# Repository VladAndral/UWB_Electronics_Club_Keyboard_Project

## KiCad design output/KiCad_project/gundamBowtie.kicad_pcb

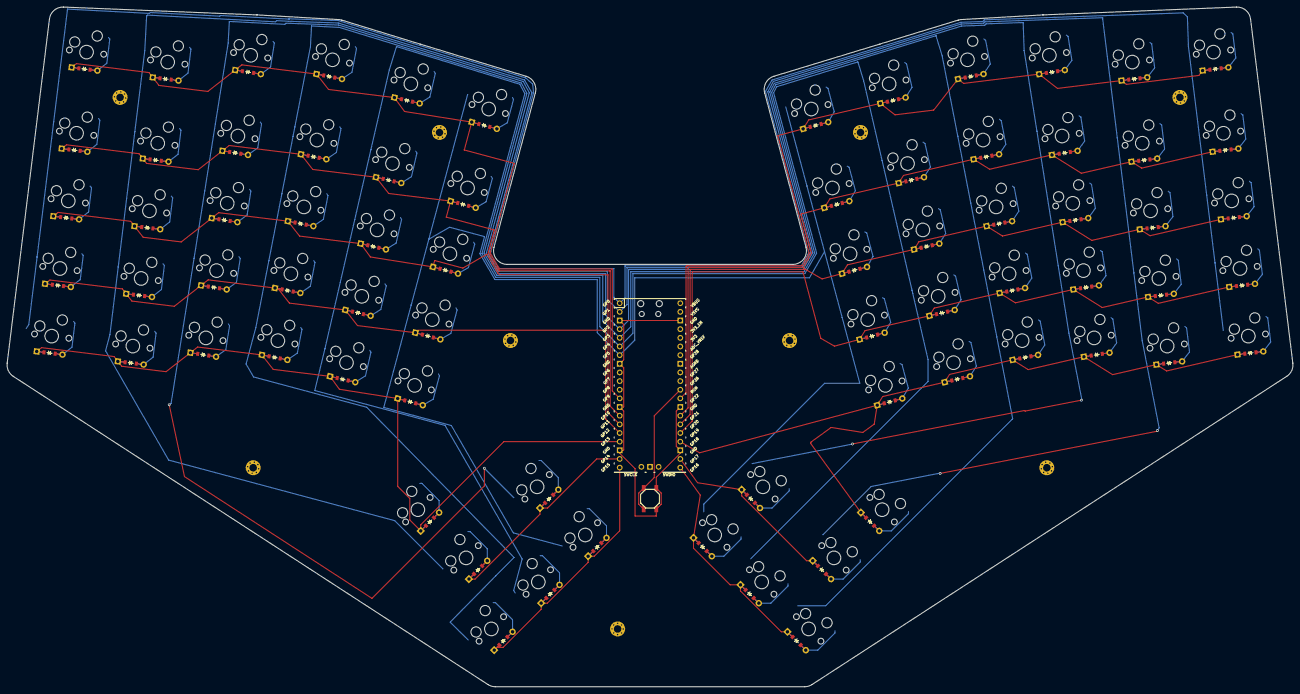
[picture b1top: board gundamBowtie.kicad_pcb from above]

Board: 2 copper layers, 377.5 x 199.5 mm, 155 parts (0 on the bottom side), 94 nets.

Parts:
B1: SW_TACT_ALPS_SKQGABE010
D1, D2, D3, D4, D5, D6, D7, D8, D9, D10, D11, D12, D13, D14, D15, D16, D17, D18, D19, D20, D21, D22, D23, D24, D25, D26, D27, D28, D29, D30, D31, D32, D33, D34, D35, D36, D37, D38, D39, D40, D41, D42, D43, D44, D45, D46, D47, D48, D49, D50, D51, D52, D53, D54, D55, D56, D57, D58, D59, D60, D61, D62, D63, D64, D65, D66, D67, D68, D69, D70, D71, D72: ComboDiode
S1, S2, S3, S4, S5, S6, S7, S8, S9, S10, S11, S12, S13, S14, S15, S16, S17, S18, S19, S20, S21, S22, S23, S24, S25, S26, S27, S28, S29, S30, S31, S32, S33, S34, S35, S36, S37, S38, S39, S40, S41, S42, S43, S44, S45, S46, S47, S48, S49, S50, S51, S52, S53, S54, S55, S56, S57, S58, S59, S60, S61, S62, S63, S64, S65, S66, S67, S68, S69, S70, S71, S72: MX
_1: RPi_Pico_SMD_TH
_2, _3, _4, _5, _6, _7, _8, _9, _10: MountingHole_2.2mm_M2_Pad_Via

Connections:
GND: B1.1, _1.3, _1.8, _1.13, _1.18, _1.23, _1.28, _1.38
GP0: S1.1, S2.1, S3.1, S4.1, S5.1, S37.1, S38.1, S39.1, S40.1, S41.1, _1.1
GP1: S6.1, S7.1, S8.1, S9.1, S10.1, S31.1, S32.1, S42.1, S43.1, S44.1, S45.1, S46.1, S67.1, S68.1, _1.2
GP2: S11.1, S12.1, S13.1, S14.1, S15.1, S33.1, S47.1, S48.1, S49.1, S50.1, S51.1, S69.1, _1.4
GP3: S16.1, S17.1, S18.1, S19.1, S20.1, S34.1, S52.1, S53.1, S54.1, S55.1, S56.1, S70.1, _1.5
GP4: S21.1, S22.1, S23.1, S24.1, S25.1, S35.1, S57.1, S58.1, S59.1, S60.1, S61.1, S71.1, _1.6
GP5: S26.1, S27.1, S28.1, S29.1, S30.1, S36.1, S62.1, S63.1, S64.1, S65.1, S66.1, S72.1, _1.7
GP9: D5.1, D10.1, D15.1, D20.1, D25.1, D30.1, _1.12
GP10: D4.1, D9.1, D14.1, D19.1, D24.1, D29.1, _1.14
GP11: D3.1, D8.1, D13.1, D18.1, D23.1, D28.1, _1.15
GP12: D2.1, D7.1, D12.1, D17.1, D22.1, D27.1, _1.16
GP13: D1.1, D6.1, D11.1, D16.1, D21.1, D26.1, D32.1, _1.17
GP14: D31.1, D33.1, _1.19
GP15: D34.1, D35.1, D36.1, _1.20
GP16: D70.1, D71.1, D72.1, _1.21
GP17: D67.1, D69.1, _1.22
GP18: D37.1, D42.1, D47.1, D52.1, D57.1, D62.1, D68.1, _1.24
GP19: D38.1, D43.1, D48.1, D53.1, D58.1, D63.1, _1.25
GP20: D39.1, D44.1, D49.1, D54.1, D59.1, D64.1, _1.26
GP21: D40.1, D45.1, D50.1, D55.1, D60.1, D65.1, _1.27
GP22: D41.1, D46.1, D51.1, D56.1, D61.1, D66.1, _1.29
RUN: B1.2, _1.30
index_bottom: D21.2, S21.2
index_function: D25.2, S25.2
index_home: D22.2, S22.2
index_number: D24.2, S24.2
index_top: D23.2, S23.2
inner_bottom: D26.2, S26.2
inner_function: D30.2, S30.2
inner_home: D27.2, S27.2
inner_number: D29.2, S29.2
inner_top: D28.2, S28.2
keysNextToBigPart2_bottom: D35.2, S35.2
keysNextToBigPart3_bottom: D36.2, S36.2
keysNextToBig_bottom: D34.2, S34.2
left_middle: D31.2, S31.2
left_top: D32.2, S32.2
middle_bottom: D16.2, S16.2
middle_function: D20.2, S20.2
middle_home: D17.2, S17.2
middle_number: D19.2, S19.2
middle_top: D18.2, S18.2
mirror_index_bottom: D57.2, S57.2
mirror_index_function: D61.2, S61.2
mirror_index_home: D58.2, S58.2
mirror_index_number: D60.2, S60.2
mirror_index_top: D59.2, S59.2
mirror_inner_bottom: D62.2, S62.2
mirror_inner_function: D66.2, S66.2
mirror_inner_home: D63.2, S63.2
mirror_inner_number: D65.2, S65.2
mirror_inner_top: D64.2, S64.2
mirror_keysNextToBigPart2_bottom: D71.2, S71.2
mirror_keysNextToBigPart3_bottom: D72.2, S72.2
mirror_keysNextToBig_bottom: D70.2, S70.2
mirror_left_middle: D67.2, S67.2
mirror_left_top: D68.2, S68.2
mirror_middle_bottom: D52.2, S52.2
mirror_middle_function: D56.2, S56.2
mirror_middle_home: D53.2, S53.2
mirror_middle_number: D55.2, S55.2
mirror_middle_top: D54.2, S54.2
mirror_mods_bottom: D37.2, S37.2
mirror_mods_function: D41.2, S41.2
mirror_mods_home: D38.2, S38.2
mirror_mods_number: D40.2, S40.2
mirror_mods_top: D39.2, S39.2
mirror_pinky_bottom: D42.2, S42.2
mirror_pinky_function: D46.2, S46.2
mirror_pinky_home: D43.2, S43.2
mirror_pinky_number: D45.2, S45.2
mirror_pinky_top: D44.2, S44.2
mirror_right_middle: D69.2, S69.2
mirror_ring_bottom: D47.2, S47.2
mirror_ring_function: D51.2, S51.2
mirror_ring_home: D48.2, S48.2
mirror_ring_number: D50.2, S50.2
mirror_ring_top: D49.2, S49.2
mods_bottom: D1.2, S1.2
mods_function: D5.2, S5.2
mods_home: D2.2, S2.2
mods_number: D4.2, S4.2
mods_top: D3.2, S3.2
pinky_bottom: D6.2, S6.2
pinky_function: D10.2, S10.2
pinky_home: D7.2, S7.2
pinky_number: D9.2, S9.2
pinky_top: D8.2, S8.2
right_middle: D33.2, S33.2
ring_bottom: D11.2, S11.2
ring_function: D15.2, S15.2
ring_home: D12.2, S12.2
ring_number: D14.2, S14.2
ring_top: D13.2, S13.2

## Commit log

2024-12-18 Adding files to github
2024-12-18 Completed traces for pcb
2024-12-19 gerbers
2024-12-19 gerbersPt.2
2025-07-01 cosmetics
